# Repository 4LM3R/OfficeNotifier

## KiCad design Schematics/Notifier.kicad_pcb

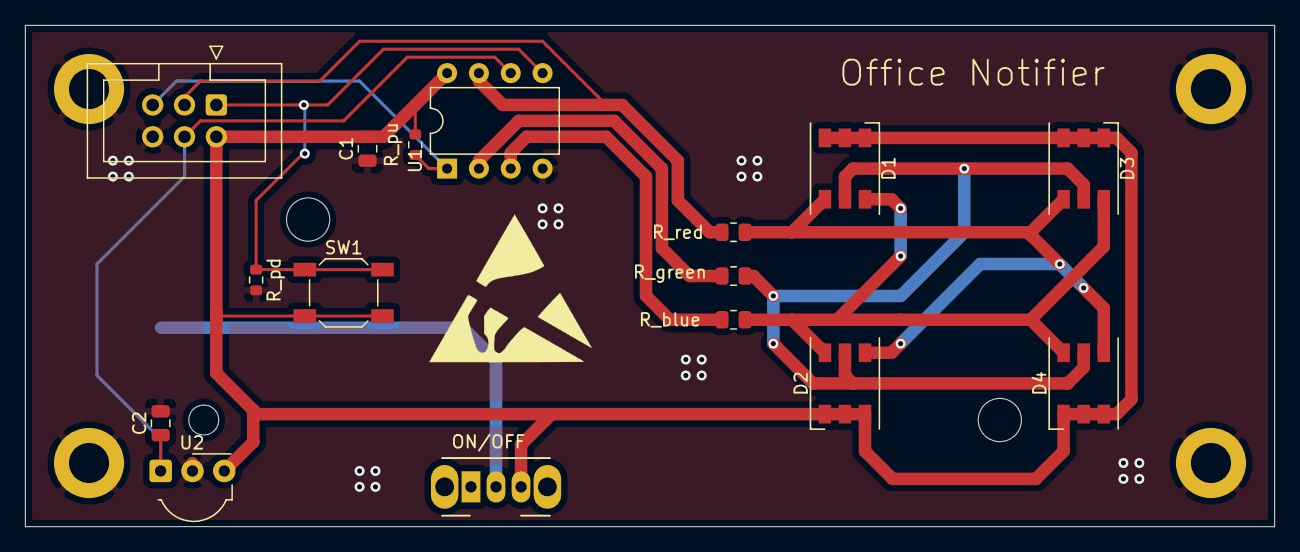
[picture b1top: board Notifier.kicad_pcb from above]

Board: 2 copper layers, 99.7 x 40.0 mm, 22 parts (1 on the bottom side), 12 nets.

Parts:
C1, C2: 4.7u; C_0805_2012Metric
D1, D2, D3, D4: HL-AF-5060H203BC-3-S1-THL; LED_WS2812_PLCC6_5.0x5.0mm_P1.6mm
FID1: Fiducial; ESD-Logo_13.2x12mm_SilkScreen
H1, H2, H3, H4: MountingHole_Pad; MountingHole_3.2mm_M3_DIN965_Pad
J1: Conn_01x02; BatteryHolder_Keystone_1042_1x18650
J2: AVR-ISP-6; IDC-Header_2x03_P2.54mm_Vertical
ON/OFF: SW_DIP_x01; SW_CuK_OS102011MA1QN1_SPDT_Angled
R_blue: 0; R_0805_2012Metric
R_green: 0; R_0805_2012Metric
R_pd: 100k; R_0603_1608Metric
R_pu: 100k; R_0603_1608Metric
R_red: 10; R_0805_2012Metric
SW1: SW_MEC_5E; SW_SPST_SKQG_WithoutStem
U1: ATtiny25V-10PU; DIP-8_W7.62mm
U2: TSOP17xx; Vishay_MOLD-3Pin

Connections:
/!RST: J2.5, R_pu.2, U1.1
/IR_out: C2.1, J2.4, U1.6, U2.1
/LED_blue: R_blue.2, U1.3
/LED_green: R_green.2, U1.2
/LED_red: J2.3, R_red.2, U1.7
/MOSI: J2.1, R_pd.1, SW1.1, U1.5
GND: C1.1, C2.2, H1.1, H2.1, H3.1, H4.1, J1.2, J2.6, R_pd.2, U1.4, U2.2
unnamed: D1.4, D2.4, D3.4, D4.4, R_red.1
unnamed: D1.5, D2.5, D3.5, D4.5, R_green.1
unnamed: D1.6, D2.6, D3.6, D4.6, R_blue.1
unnamed: J1.1, ON/OFF.2
VCC: C1.2, D1.1, D1.2, D1.3, D2.1, D2.2, D2.3, D3.1, D3.2, D3.3, D4.1, D4.2, D4.3, J2.2, ON/OFF.3, R_pu.1, SW1.2, U1.8, U2.3

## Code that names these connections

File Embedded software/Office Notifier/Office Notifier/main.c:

/*
 *	Office Notifier
 *	main.c
 *  Created: 11/19/2020 6:44:11 PM
 *  Author: Almer de Vries
 */ 

/*
Spiekbriefje
	PB0 -> Switch		PORTB = 0b00000001;		// set PB3 high
	PB1 -> IR_out		PORTB = 0b00000010;		// set PB3 high
	PB2 -> LED_red		PORTB = 0b00000100;		// set PB3 high
	PB3 -> LED_green	PORTB = 0b00001000;		// set PB3 high
	PB4 -> LED_blue		PORTB = 0b00010000;		// set PB3 high
*/

#include <xc.h>
#include <avr/io.h>
#include <avr/interrupt.h>
#include <avr/delay.h>

//#include <util/delay.h>

int i, l;
int button, button_prev, ir, state, ee = 0;

#define 	F_CPU   1000000UL

int main(void)
{
	DDRB = (1<<DDB4)|(1<<DDB3)|(1<<DDB2); //Data Direction Register B
	PORTB = 0b00011000;	//Groen
	_delay_ms(500);
	PORTB = 0b00010100;	//Rood
	_delay_ms(500);
	PORTB = 0b00001100;	//Blauw
	_delay_ms(500);
	PORTB = 0b00011100;	//Uit
	_delay_ms(2000);
	PORTB = 0b00011000;	//Groen
				
	while(1) 
	{
		if (PINB & (1<<PORTB0) && button_prev == 0){
			
			button_prev = 1;
			
				if(state < 3){
					state++;
				}
				else{
					state = 1;
				}
				setled();
				
			_delay_ms(300);
				
		}
		else if (PINB & (1<<PORTB0) && button_prev == 1){
			ee++;
			
			if(ee == 1000){
				easteregg();
				setled();
			}
			
			_delay_ms(10);
		}
		
		else if (!(PINB & (1<<PORTB0)) && button_prev == 1){
			button_prev = 0;
			ee = 0;
		}	
	}
}

void setled(){
	switch (state){
		case(1):
		PORTB = 0b00010100;	//Rood
		break;
					
		case(2):
		PORTB = 0b00010000;	//Oranje
		break;
					
		case(3):
		PORTB = 0b00011000;	//Groen
		break;
					
		default:
		state = 1;
		break;
	}
}
void easteregg(){
	for(int i = 0; i < 20; i++){
		PORTB = 0b00011000;	//Groen
		_delay_ms(100);
		PORTB = 0b00010100;	//Rood
		_delay_ms(100);
		PORTB = 0b00001100;	//Blauw
		_delay_ms(100);
		PORTB = 0b00000100;	//Paars
		_delay_ms(100);
		PORTB = 0b00001000;	//Lichtblauw
		_delay_ms(100);
		PORTB = 0b00010000;	//Oranje
		_delay_ms(100);
		PORTB = 0b00011100;	//Uit
	}
}

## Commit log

2020-11-29 Test
